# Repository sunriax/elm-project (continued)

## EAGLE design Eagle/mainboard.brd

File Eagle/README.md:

# elmProject EAGLE files
## Mainboard

### Files
1. Library:
		mainboard.lbr

1. Schematic:
		mainboard.sch
		schematic.pdf

1. Board:
		mainboard.brd
		layout.pdf

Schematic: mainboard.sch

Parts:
ANT1: SWRA092B
C1, C14, C15, C17, C94, C95, C96, C97, C99, C100, C122, C183, C186, C189, C193, C196, C199, C202, C206, C209, C212, C215, C228: 100n; C0402
C2, C5, C6, C7, C20, C21, C22, C29, C30, C34, C35, C36, C43, C51, C52, C53, C62, C63, C64, C73, C74, C75, C85, C86: 47n; C0402
C3, C4, C8, C9, C10, C23, C24, C25, C31, C37, C38, C39, C44, C54, C55, C56, C65, C66, C69, C76, C77, C78, C247: 470n; C0402
C11, C12, C26, C27, C32, C40, C41, C49, C57, C58, C70, C71, C79, C80: 4,7u; C0603
C13, C42, C59, C72, C81, C225, C226: 100u; C1206
C16: 4.7u; C0603
C18, C28, C33, C50, C250: 47u; C0603
C19, C48, C236, C237, C238, C248, C249: 470n; C0603
C45, C82, C83, C84, C87, C89, C90, C123, C124, C125, C182, C185, C188, C192, C195, C198, C201, C205, C208, C211, C214, C233, C234, C235, C243, C244, C245, C246: 10n; C0402
C46, C47: 47n; C0603
C60, C61, C177, C227, C251, C266, C267, C268, C269, C270: 10n; C0603
C67, C111, C118, C158, C159, C160: 4,7µF; C0603
C68, C142, C143, C161: 10µF; C0603
C88, C91, C203, C216, C229: 10u; C0603
C92, C93: 12p; C0402
C98: 10p; C0402
C101, C180, C190: 1u; C0603
C102: 1u; C0402
C103: 2u2; C0603
C104, C119, C178, C179: 18p; C0402
C105, C106, C112, C113: 220pF; C0603
C107, C108, C109, C110, C114, C115, C116, C117: 22pF; C0603
C120, C121: 1p; C0402
C126, C127: 0,1µF; C0603
C128, C131, C132, C133, C135, C136, C137, C138, C139: 1µF; C0603
C129, C130: 33pF; C0402
C134: 2,2µF; C0603
C145, C146: 22µF; C0603
C148, C149: 47µF; C0603
C151, C152: 68µF; C1206
C154, C156: 4,7µ; C0603
C157: 2,2µF; C1206K
C181, C184, C187, C191, C194, C197, C200, C204, C207, C210, C213: 1n; C0402
C217, C218, C219, C220, C221, C222, C223, C224, C230, C231, C232, C239, C240, C241, C242: 47p; C0402
C252: 22p; C0402
D1, D4, D5, D6, D7, D10, D11, D12, D38, D39, D40, D41: WE-TVS_824015; WE-TVS_SOT23-6L
D2, D8, D35, D36, D42: WE-TVS_824011; WE-TVS_SOT23-5L
D3, D37: BAT6202VH6327XTSA1-ND; SOD523
D9: CZSH5-40-TR-ND; SOT223
FRAME1, FRAME2, FRAME3, FRAME4, FRAME5, FRAME6, FRAME7, FRAME8, FRAME9, FRAME10: HTL-A3-HA3H; HTL-A3-H
G1: 10MM_SM_COIN_CELL_CLIP
IC1: S25FL128P
IC5: FT240X; SSOP24-0.635-8.65X4MM
IC6: CC2540; QFN40-6X6
IC7: Arietta/FPGA; LT8602
IC8: Boards; LT8602
IC9: TUSB4041I; HTQFP-64-EXP
IC10: LTC2947
IC11: 74AHC1G32DCK; SC70-5
IC12, IC13: 74AHC1G04DCK; SC70-5
IC14: EEPROM; SOIC-8
IC16: MT48LC16M16A2; TSOP54-400
K1: 61001221121
K2: 61000418221
K3: 691321100002
K4, K5: 61300511821
L1, L2: 1u; L2012C
L3: 6n8; L2012C
L4, L7, L10: 220 Ohm @ 100 Mhz; WE-KI_0603_B
L5, L6: 4,3n; WE-KI_0402A
L8: 12n; WE-KI_0402A
L13, L17: 10µH; NR6028T100M
L14, L18: 4,7µH; NR6028T100M
L15, L21: 2,2µH; IHHP-0806AZ-01
L16, L24: 1,1µH; SRN3012TA
LED_BANK1_FAULT, LED_BANK1_ONLINE, LED_BANK2_FAULT, LED_BANK2_ONLINE: 0.7; SMARTLED-TTW
LED_BLUETOOTH: 0.7; SMARTLED-TTW
LED_DONE: 0.7; SMARTLED-TTW
PAD1, PAD2, PAD3, PAD4, PAD5, PAD6, PAD7, PAD8, PAD9, PAD10, PAD11, PAD12, PAD13, PAD14, PAD15, PAD16: SMD2; SMD1,27-2,54
Q1: SPD30P06PTO252; TO252
Q2: 24MHz; CTS406
Q3: 32MHz; CTS402_3.2X2.5
R1, R20, R25: 33; R0402
R2, R21, R61: 0; R0402
R3, R9, R10, R15: 4k7; R0402
R4, R5, R6, R14, R56, R58: 1k; R0402
R7: 200; R0402
R8, R11, R12, R13, R16, R18, R19, R34, R35, R40, R41, R42: 100; R0402
R17, R22, R23, R24: 330; R0402
R26, R27, R28, R29, R30, R31, R32, R33: 10Ohm; R0603
R36, R62: 1; R0402
R37, R38, R95, R107: 10k; R0603
R39: 56k; R0603
R43: 1M; R0805
R44: 9k53 1%; R0603
R45: 90k9 1%; R0603
R46: 10k 1%; R0603
R47, R48, R49, R50, R51, R52, R53, R54: 27; R0402
R55: 25; R0402
R57: 1k; R0603
R63, R64: 1k5; R0402
R65: 10k; R0402
R84, R96, R103: 68k; R0603
R85, R97: 400k; R0603
R86, R98: 100k; R0603
R87, R99: 715k; R0603
R88, R90, R92, R94, R100, R102, R104, R106: 180k; R0603
R89, R101: 412k; R0603
R91: 47k; R0603
R93, R105: 226k; R0603
R120, R121: 22Ohm; R0603
R122: 100k; R1206
R123: 2Ohm; R1206
R124, R125: 4,02k; R1206
R126: 10m; R1206
RN1, RN2, RN3, RN4, RN5, RN6, RN7, RN8, RN9, RN10, RN11, RN12, RN16, RN17, RN18, RN19, RN20, RN23, RN24, RN25, RN26, RN27, RN28, RN29, RN30, RN31, RN32, RN33, RN34: 100; EXBV8V
RN15: 10k; EXBV8V
RN21, RN22, RN36, RN37, RN38, RN39, RN40, RN41, RN42, RN43: 33; EXBV8V
RN35: 1k; EXBV8V
RN44: 25; EXBV8V
S1, S2, S3: TASTER_SMD
TP3, TP4: PTR1TP06SQ; TP06SQ
U1: XC7A100TFTG256; FT256
U$1: ARIETTA
U$4, U$11: NTD4969NT4G_N-MOS; TO252
U$5, U$6: ASE
U$7, U$8: NUF2221W1
U$9, U$10: MF-SMDF200; MF-SMDF050
X1, X2, X3, X4: FAB64S
X5: ABLS2-4.000MHZ-D4Y-T
X6, X7: USB-A003
X8: JMP2

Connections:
$N299: C225.1, C226.1, C227.2, D36.3 (1), D36.4 (2), D36.5 (VDD), U$10.2, X6.4, X7.4
+1V1_EXT: C116.1, C152.1, L7.1, L24.P$2 (OUT), PAD16.1, R33.2
+1V1_HUB: C194.1, C195.1, C196.1, C197.1, C198.1, C199.1, C200.1, C201.1, C202.1, C203.1, C204.1, C205.1, C206.1, C207.1, C208.1, C209.1, C210.1, C211.1, C212.1, C213.1, C214.1, C215.1, C216.1, IC9.19 (VDD), IC9.25 (VDD), IC9.37 (VDD), IC9.45 (VDD), IC9.53 (VDD), IC9.60 (VDD), IC9.63 (VDD), L7.2
+1V8_EXT: C117.1, C149.1, D6.1, D38.1, D39.1, D40.3 (2), L21.P$2 (OUT), PAD14.1, R32.2, X1.B32, X2.B32, X3.B32, X4.B32
+1V8_INT: C20.1, C21.1, C22.1, C23.1, C24.1, C25.1, C26.1, C27.1, C28.1, C110.1, C148.1, L1.2, L15.P$2 (OUT), PAD6.1, R28.2, U1.F8 (VCCBATT_0), U1.G10 (VCCAUX), U1.J10 (VCCAUX), U1.K11 (VCCAUX), U1.L10 (VCCAUX)
+1V_INT: C29.1, C30.1, C31.1, C32.1, C33.1, C34.1, C35.1, C36.1, C37.1, C38.1, C39.1, C40.1, C41.1, C42.1, C43.1, C109.1, C151.1, L16.P$2 (OUT), PAD8.1, R29.2, U1.E10 (VCCBRAM), U1.F7 (VCCINT), U1.F9 (VCCINT), U1.F11 (VCCBRAM), U1.G6 (VCCINT), U1.H9 (VCCINT), U1.J6 (VCCINT), U1.K9 (VCCINT), U1.L8 (VCCINT)
+3V3_ARIETTA: C82.2, C83.2, C89.2, C90.2, D3.C, D4.5 (VDD), D5.5 (VDD), D7.5 (VDD), D8.5 (VDD), R37.1, RN15.5 (2), RN15.6 (2), RN15.7 (2), RN15.8 (2), U$1.5 (3V3)
+3V3_BLUETOOTH: C94.2, C95.2, C96.2, C97.2, C98.2, C99.2, C100.2, C101.2, C103.1, C123.2, C124.2, C125.2, C252.2, D10.5 (VDD), D11.5 (VDD), D12.5 (VDD), IC6.4 (DVDD_USB), IC6.10 (DVDD2), IC6.21 (AVDD5), IC6.24 (AVDD3), IC6.27 (AVDD2), IC6.28 (AVDD1), IC6.29 (AVDD4), IC6.31 (AVDD6), IC6.39 (DVDD1), L4.2
+3V3_EXT: C60.1, C61.1, C62.1, C63.1, C64.1, C65.1, C66.1, C69.1, C70.1, C71.1, C72.1, C73.1, C74.1, C75.1, C76.1, C77.1, C78.1, C79.1, C80.1, C81.1, C115.1, C118.1, C146.1, C159.1, C177.2, C251.1, D1.5 (VDD), D2.5 (VDD), D6.6 (4), D35.5 (VDD), D38.6 (4), D39.6 (4), D40.6 (4), D42.4 (2), D42.5 (VDD), IC8.BIAS, IC8.PVIN3, IC8.PVIN4, IC11.5 (VCC), IC12.5 (VCC), IC13.5 (VCC), L10.1, L18.2 (OUT), PAD11.1, R2.2, R31.2, R107.1, U1.A6 (VCCO_35), U1.A16 (VCCO_15), U1.B3 (VCCO_35), U1.B13 (VCCO_15), U1.C10 (VCCO_15), U1.D7 (VCCO_35), U1.E4 (VCCO_35), U1.E14 (VCCO_15), U1.F1 (VCCO_35), U1.H15 (VCCO_15), U1.J2 (VCCO_35), U1.J12 (VCCO_15), X1.B30, X2.B30, X3.B30, X4.B30, X8.1
+3V3_HUB: C181.1, C182.1, C183.1, C184.1, C185.1, C186.1, C187.1, C188.1, C189.1, C190.1, C191.1, C192.1, C193.1, C228.1, IC9.2 (VDD33), IC9.20 (VDD33), IC9.31 (VDD33), IC9.48 (VDD33), IC14.8 (VCC), L10.2, R56.1, R57.2, R63.1, R64.2, U$7.5 (VBUS), U$8.5 (VBUS)
+3V3_INT: C1.1, C2.2, C3.2, C4.2, C5.1, C6.1, C7.1, C8.1, C9.1, C10.1, C11.1, C12.1, C13.1, C14.1, C15.1, C16.1, C18.1, C19.1, C51.1, C52.1, C53.1, C54.1, C55.1, C56.1, C57.1, C58.1, C59.1, C84.1, C85.1, C86.1, C87.1, C108.1, C111.1, C122.1, C131.1, C145.1, C158.1, C230.1, C231.1, C232.1, C233.1, C234.1, C235.1, C236.1, C237.1, C238.1, C239.1, C240.1, C241.1, C242.1, C243.1, C244.1, C245.1, C246.1, C247.1, C248.1, C249.1, C250.1, C270.2, D37.C, D41.5 (VDD), IC1.VCC, IC5.18 (VCC), IC7.BIAS, IC7.PVIN3, IC7.PVIN4, IC10.AD0, IC10.OVDD, IC16.1 (VDD), IC16.3 (VDDQ), IC16.9 (VDDQ), IC16.14 (VDD), IC16.27 (VDD), IC16.43 (VDDQ), IC16.49 (VDDQ), K2.3, L14.2 (OUT), PAD4.1, R3.2, R5.2, R6.2, R7.1, R9.1, R10.1, R14.1, R15.1, R27.2, R38.1, R65.2, R95.1, U1.L6 (VCCO_0), U1.L16 (VCCO_14), U1.M3 (VCCO_34), U1.M13 (VCCO_14), U1.N10 (VCCO_14), U1.P7 (VCCO_14), U1.R4 (VCCO_34), U1.R14 (VCCO_14), U1.T1 (VCCO_34), U1.T11 (VCCO_14), U$5.1 (TRI), U$5.4 (VDD), U$6.1 (TRI), U$6.4 (VDD)
+5V_EXT: C114.1, C143.1, C229.1, C266.2, C267.2, C268.2, C269.2, D6.3 (2), D6.5 (VDD), D38.3 (2), D38.5 (VDD), D39.3 (2), D39.5 (VDD), D40.1, D40.5 (VDD), L17.2 (OUT), PAD10.1, R30.2, R45.1, U$10.1, X1.B31, X2.B31, X3.B31, X4.B31
+5V_INT: C46.1, C47.1, C48.1, C49.1, C50.1, C107.1, C142.1, L13.2 (OUT), PAD1.1, R26.2, U$1.1 (5V)
ACDRVPIN: K4.2, Q1.1 (G), R122.2, R124.1
ACN: C132.1, C133.1, IC10.AVCC, IC10.DVCC, IC10.IP_1 (IP), IC10.IP_2 (IP), IC10.IP_3 (IP), IC10.IP_4 (IP), IC10.IP_5 (IP), IC10.IP_6 (IP), K5.1, K5.2, K5.3, Q1.3 (D), R126.2
ACPPIN: K5.4, R126.1, U$11.3 (D)
ARIETTA_IO0: D4.1, RN1.8 (2), X1.B7, X2.B7
ARIETTA_IO1: D4.3 (2), RN1.7 (2), X1.A6, X2.A7
ARIETTA_IO2: D4.4 (3), RN1.6 (2), X1.B6, X2.B6
ARIETTA_IO3: D4.6 (4), RN1.5 (2), X1.B5, X2.A6
ARIETTA_IO4: D5.3 (2), RN2.5 (2), X1.A5, X2.B5
ARIETTA_IO5: D5.1, RN2.6 (2), X1.B4, X2.A5
AVCCPIN: D9.4 (C), K4.3, Q1.2 (S), R123.2, U$4.3 (D)
BANK1_AD*N0: RN3.5 (2), X3.B22
BANK1_AD*N1: RN3.8 (2), X3.B24
BANK1_AD*N2: RN4.8 (2), X3.A26
BANK1_AD*N3: RN5.7 (2), X3.A21
BANK1_AD*N4: RN6.7 (2), X3.A28
BANK1_AD*N5: RN6.5 (2), X3.B27
BANK1_AD*N6: RN7.8 (2), X3.A24
BANK1_AD*N7: RN7.5 (2), X3.B26
BANK1_AD*P0: RN3.6 (2), X3.A22
BANK1_AD*P1: RN3.7 (2), X3.B23
BANK1_AD*P2: RN4.7 (2), X3.A25
BANK1_AD*P3: RN5.8 (2), X3.B21
BANK1_AD*P4: RN6.8 (2), X3.B28
BANK1_AD*P5: RN6.6 (2), X3.A27
BANK1_AD*P6: RN7.7 (2), X3.A23
BANK1_AD*P7: RN7.6 (2), X3.B25
BANK1_FAULT: IC12.2 (I), R41.2, U1.E6 (IO_0_35)
BANK1_MRCC/SRCC0: RN8.6 (2), X1.A25, X4.B25
BANK1_MRCC/SRCC1: RN8.5 (2), X1.B25, X4.B24
BANK1_MRCC/SRCC2: RN8.7 (2), X1.B26, X4.B26
BANK1_MRCC/SRCC3: RN8.8 (2), X1.A26, X4.B27
BANK1_MRCC/SRCC4: RN9.7 (2), X1.B22, X4.A21
BANK1_MRCC/SRCC5: RN9.8 (2), X1.B21, X4.A20
BANK1_MRCC/SRCC6: RN9.6 (2), X1.A22, X2.B22
BANK1_MRCC/SRCC7: RN9.5 (2), X1.A23, X2.B23
BANK1_T0_0: RN4.5 (2), X1.B24, X4.B23
BANK1_T0_1: RN4.6 (2), X1.A24, X4.A23
BANK1_T0_2: RN5.6 (2), X1.B20, X4.B20
BANK1_T0_3: RN5.5 (2), X1.B23
BANK1_T2_0: RN10.8 (2), X1.A21, X2.B21, X4.A17
BANK1_T2_1: RN10.7 (2), X1.A20, X2.B20, X4.B17
BANK1_T2_2: RN10.6 (2), X1.B19, X2.B19, X4.A14
BANK1_T2_3: RN11.7 (2), X1.A18
BANK1_T2_4: RN10.5 (2), X1.A19, X2.B18, X4.B14
BANK1_T2_5: RN11.8 (2), X1.B18
BANK1_T2_6: RN11.6 (2), X1.B17
BANK1_T2_7: RN11.5 (2), X1.A17, X2.B17
BANK1_T3_0: RN12.8 (2), X1.A28, X2.B28
BANK1_T3_1: RN12.7 (2), X1.B28, X2.B27
BANK1_T3_2: RN12.6 (2), X1.A27, X2.B26
BANK1_T3_3: RN12.5 (2), X1.B27, X2.B25
BANK2_A0: RN30.6 (2), X1.A15, X3.A12, X4.A10
BANK2_A1: RN30.5 (2), X1.B14, X3.B11, X4.B9
BANK2_A2: RN31.8 (2), X1.B12, X3.B9, X4.B7
BANK2_A3: RN31.6 (2), X1.B13, X3.B10, X4.B8
BANK2_A4: RN31.7 (2), X1.A12, X3.A9, X4.A7
BANK2_A5: RN31.5 (2), X1.A13, X3.A10, X4.A8
BANK2_A6: RN32.7 (2), X1.B11, X3.B8, X4.B6
BANK2_A7: RN32.8 (2), X1.A11, X3.A8, X4.A6
BANK2_A8: RN32.5 (2), X1.B9, X3.B7, X4.B5
BANK2_A9: RN32.6 (2), X1.B10, X3.A7, X4.A5
BANK2_A10: RN33.8 (2), X1.A14, X3.A11, X4.A9
BANK2_A11: RN33.7 (2), X1.B15, X3.B12, X4.B10
BANK2_A12: RN33.5 (2), X1.B16, X4.A16
BANK2_A13: RN33.6 (2), X1.A16, X4.A15
BANK2_AD*N0: RN23.6 (2), X3.B19
BANK2_AD*N1: RN23.5 (2), X3.A19
BANK2_AD*N2: RN24.7 (2), X3.B13
BANK2_AD*N3: RN25.8 (2), X3.A15
BANK2_AD*N4: RN26.7 (2), X3.A16
BANK2_AD*N5: RN26.8 (2), X3.B16
BANK2_AD*N6: RN27.6 (2), X3.B17
BANK2_AD*N7: RN27.5 (2), X3.A17
BANK2_AD*P0: RN23.8 (2), X3.B20
BANK2_AD*P1: RN23.7 (2), X3.A20
BANK2_AD*P2: RN24.8 (2), X3.A13
BANK2_AD*P3: RN25.7 (2), X3.B15
BANK2_AD*P4: RN26.5 (2), X3.B14
BANK2_AD*P5: RN26.6 (2), X3.A14
BANK2_AD*P6: RN27.8 (2), X3.B18
BANK2_AD*P7: RN27.7 (2), X3.A18
BANK2_FAULT: IC13.2 (I), R42.2, U1.D10 (IO_0_15)
BANK2_MRCC/SRCC0: RN28.8 (2), X2.A10, X3.A5
BANK2_MRCC/SRCC1: RN28.7 (2), X2.B10, X3.B5
BANK2_MRCC/SRCC2: RN28.6 (2), X2.A8, X3.B2
BANK2_MRCC/SRCC3: RN28.5 (2), X2.B8, X3.B1
BANK2_MRCC/SRCC4: RN29.7 (2), X2.A9, X3.B4
BANK2_MRCC/SRCC5: RN29.8 (2), X2.B9, X3.B3
BANK2_MRCC/SRCC6: RN29.6 (2), X2.B11, X3.B6
BANK2_MRCC/SRCC7: RN29.5 (2), X2.A11, X3.A6
BANK2_T0_0: RN24.6 (2), X2.A12, X4.A11
BANK2_T0_1: RN24.5 (2), X2.B12, X4.B11
BANK2_T0_2: RN25.5 (2), X2.A14, X4.A13
BANK2_T0_3: RN25.6 (2), X2.A13, X4.B13
BANK2_T2_0: RN30.7 (2), X2.A15, X4.B15
BANK2_T2_1: RN30.8 (2), X2.A16, X4.B16
BANK2_T3_0: RN34.7 (2), X1.A8, X2.B14
BANK2_T3_1: RN34.8 (2), X1.A7, X2.B13
BANK2_T3_2: RN34.6 (2), X1.A9, X2.B15
BANK2_T3_3: RN34.5 (2), X1.A10, X2.B16
BANK_FAULT: D35.4 (2), R62.2, X1.B29, X2.B29, X3.B29, X4.B29
BLUETOOTH_EXT0: D11.1, RN18.8 (2), X2.A17, X4.A18
BLUETOOTH_EXT1: D11.3 (2), RN18.7 (2), X2.A18, X4.B18
BLUETOOTH_EXT2: D10.6 (4), RN18.6 (2), X2.A22, X4.B22
BLUETOOTH_EXT3: D10.4 (3), RN18.5 (2), X2.A21, X4.B21
BLUETOOTH_EXT4: D10.1, RN19.8 (2), X2.A20, X4.A19
BLUETOOTH_EXT5: D10.3 (2), RN19.7 (2), X2.A19, X4.B19
BLUETOOTH_EXT6: D11.6 (4), RN19.6 (2), X2.A23, X4.A22
BLUETOOTH_EXT7: D11.4 (3), RN19.5 (2), X2.A24, X4.A24
BLUETOOTH_EXT8: D12.1, RN20.8 (2), X2.A25, X4.A25
BLUETOOTH_EXT9: D12.3 (2), RN20.7 (2), X2.A26, X4.A26
BLUETOOTH_EXT10: D12.6 (4), RN20.6 (2), X2.A27, X4.A27
BLUETOOTH_EXT11: D12.4 (3), RN20.5 (2), X2.A28, X4.A28
BLUETOOTH_INT0: RN21.8 (2), U1.J1 (IO_L22N_T3_35)
BLUETOOTH_INT1: RN21.7 (2), U1.K1 (IO_L22P_T3_35)
BLUETOOTH_INT2: RN21.6 (2), U1.H3 (IO_L21N_T3_DQS_35)
BLUETOOTH_INT3: RN21.5 (2), U1.J3 (IO_L21P_T3_DQS_35)
BLUETOOTH_INT4: RN22.8 (2), U1.L2 (IO_L23N_T3_35)
BLUETOOTH_INT5: RN22.7 (2), U1.L3 (IO_L23P_T3_35)
BLUETOOTH_INT6: RN22.6 (2), U1.K2 (IO_L24N_T3_35)
BLUETOOTH_INT7: RN22.5 (2), U1.K3 (IO_L24P_T3_35)
BLUETOOTH_USB_DM: C222.1, IC6.3 (USB_N), R51.1
BLUETOOTH_USB_DP: C223.1, IC6.2 (USB_P), R53.1, R63.2
CMSRCPIN: K4.1, R125.1
CONFIG_CCLK: IC1.SCK, R24.1, U1.E8 (CCLK_0)
CONFIG_D00_MOSI: R12.1, U1.J13 (IO_L1P_T0_D00_MOSI_14)
CONFIG_D01_DIN: R11.2, R18.2, U1.J14 (IO_L1N_T0_D01_DIN_14)
CONFIG_D02_DQ2: R13.1, U1.K15 (IO_L2P_T0_D02_14)
CONFIG_D03_DQ3: R16.2, U1.K16 (IO_L2N_T0_D03_14)
CONFIG_DOUT: R19.2, U1.T12 (IO_L15N_T2_DQS_DOUT_CSO_B_14)
CONFIG_FCS_B: IC1.CS#, R15.2, U1.L12 (IO_L6P_T0_FCS_B_14)
DONE: R7.2, R8.1, R22.1, U1.H10 (DONE_0)
FIFO0: IC5.24 (DATA0), U1.P15 (IO_L8P_T1_D11_14)
FIFO1: IC5.4 (DATA1), U1.M14 (IO_L4N_T0_D05_14)
FIFO2: IC5.2 (DATA2), U1.N16 (IO_L7N_T1_D10_14)
FIFO3: IC5.9 (DATA3), U1.L14 (IO_L4P_T0_D04_14)
FIFO4: IC5.1 (DATA4), U1.P16 (IO_L8N_T1_D12_14)
FIFO5: IC5.7 (DATA5), U1.K13 (IO_L5P_T0_D06_14)
FIFO6: IC5.8 (DATA6), U1.L13 (IO_L5N_T0_D07_14)
FIFO7: IC5.5 (DATA7), U1.M16 (IO_L7P_T1_D09_14)
FIFO_USB_DM: C221.1, IC5.14 (USBDM), R52.1
FIFO_USB_DP: C224.1, IC5.13 (USBDP), R54.1, R64.1
FPGA_CCLK1: U1.N14 (IO_L12P_T1_MRCC_14), U$5.3 (OUT)
FPGA_CCLK2: U1.P14 (IO_L12N_T1_MRCC_14), U$6.3 (OUT)
GND: C1.2, C2.1, C3.1, C4.1, C5.2, C6.2, C7.2, C8.2, C9.2, C10.2, C11.2, C12.2, C13.2, C14.2, C15.2, C16.2, C17.2, C18.2, C19.2, C20.2, C21.2, C22.2, C23.2, C24.2, C25.2, C26.2, C27.2, C28.2, C29.2, C30.2, C31.2, C32.2, C33.2, C34.2, C35.2, C36.2, C37.2, C38.2, C39.2, C40.2, C41.2, C42.2, C43.2, C44.2, C46.2, C47.2, C48.2, C49.2, C50.2, C51.2, C52.2, C53.2, C54.2, C55.2, C56.2, C57.2, C58.2, C59.2, C60.2, C61.2, C62.2, C63.2, C64.2, C65.2, C66.2, C67.2, C68.2, C69.2, C70.2, C71.2, C72.2, C73.2, C74.2, C75.2, C76.2, C77.2, C78.2, C79.2, C80.2, C81.2, C82.1, C83.1, C84.2, C85.2, C86.2, C87.2, C88.1, C89.1, C90.1, C91.1, C92.1, C93.1, C94.1, C95.1, C96.1, C97.1, C98.1, C99.1, C100.1, C101.1, C102.2, C103.2, C105.2, C106.2, C111.2, C112.2, C113.2, C118.2, C121.2, C122.2, C123.1, C124.1, C125.1, C126.1, C127.1, C129.2, C130.2, C131.2, C132.2, C133.2, C135.2, C142.2, C143.2, C145.2, C146.2, C148.2, C149.2, C151.2, C152.2, C154.2, C156.2, C157.2, C158.2, C159.2, C160.2, C161.2, C177.1, C178.1, C179.1, C180.1, C181.2, C182.2, C183.2, C184.2, C185.2, C186.2, C187.2, C188.2, C189.2, C190.2, C191.2, C192.2, C193.2, C194.2, C195.2, C196.2, C197.2, C198.2, C199.2, C200.2, C201.2, C202.2, C203.2, C204.2, C205.2, C206.2, C207.2, C208.2, C209.2, C210.2, C211.2, C212.2, C213.2, C214.2, C215.2, C216.2, C217.1, C218.2, C219.1, C220.2, C221.2, C222.2, C223.2, C224.2, C225.2, C226.2, C227.1, C228.2, C229.2, C230.2, C231.2, C232.2, C233.2, C234.2, C235.2, C236.2, C237.2, C238.2, C239.2, C240.2, C241.2, C242.2, C243.2, C244.2, C245.2, C246.2, C247.2, C248.2, C249.2, C250.2, C251.2, C252.1, C266.1, C267.1, C268.1, C269.1, C270.1, D1.2 (GND), D2.2 (GND), D4.2 (GND), D5.2 (GND), D6.2 (GND), D7.2 (GND), D8.2 (GND), D10.2 (GND), D11.2 (GND), D12.2 (GND), D35.2 (GND), D36.2 (GND), D38.2 (GND), D39.2 (GND), D40.2 (GND), D41.2 (GND), D42.2 (GND), G1.-, IC1.GND, IC5.6 (GND), IC5.19 (GND1), IC6.1 (DGND_USB), IC6.EXP@1 (EXP16), IC6.EXP@2 (EXP16), IC6.EXP@3 (EXP16), IC6.EXP@4 (EXP16), IC6.EXP@5 (EXP16), IC6.EXP@6 (EXP16), IC6.EXP@7 (EXP16), IC6.EXP@8 (EXP16), IC6.EXP@9 (EXP16), IC6.EXP@10 (EXP16), IC6.EXP@11 (EXP16), IC6.EXP@12 (EXP16), IC6.EXP@13 (EXP16), IC6.EXP@14 (EXP16), IC6.EXP@15 (EXP16), IC6.EXP@16 (EXP16), IC7.GND_1 (GND), IC7.GND_2 (GND), IC7.GND_3 (GND), IC7.GND_4 (GND), IC7.GND_5 (GND), IC7.GND_6 (GND), IC7.GND_7 (GND), IC7.GND_8 (GND), IC7.POREN, IC7.SYNC, IC8.GND_1 (GND), IC8.GND_2 (GND), IC8.GND_3 (GND), IC8.GND_4 (GND), IC8.GND_5 (GND), IC8.GND_6 (GND), IC8.GND_7 (GND), IC8.GND_8 (GND), IC8.POREN, IC8.SYNC, IC9.EXP (GND), IC10.AGND, IC10.ALERT, IC10.DGND, IC10.DGND_2 (DGND), IC10.GPIO, IC11.3 (GND), IC12.3 (GND), IC13.3 (GND), IC14.4 (GND), IC16.6 (VSSQ), IC16.12 (VSSQ), IC16.28 (VSS), IC16.41 (VSS), IC16.46 (VSSQ), IC16.52 (VSSQ), IC16.54 (VSS), K1.1, K1.12, K2.1, K3.1, K4.4, K4.5, L2.2, L6.1, LED_BANK1_FAULT.C@1 (C), LED_BANK1_ONLINE.C@1 (C), LED_BANK2_FAULT.C@1 (C), LED_BANK2_ONLINE.C@1 (C), LED_BLUETOOTH.C@1 (C), LED_DONE.C@1 (C), R4.2, R39.2, R44.1, R46.1, R84.1, R86.1, R88.1, R90.1, R92.1, R94.1, R96.1, R98.1, R100.1, R102.1, R104.1, R106.1, R121.2, R122.1, RN35.5 (2), RN35.6 (2), RN35.7 (2), RN35.8 (2), S1.1 (S), S1.2 (S1), S2.3, S2.4 (P1), S3.3, S3.4 (P1), U1.A1 (GND), U1.A11 (GND), U1.B8 (GND), U1.C5 (GND), U1.C15 (GND), U1.D2 (GND), U1.D12 (GND), U1.E9 (GND), U1.F6 (GND), U1.F10 (GND), U1.F16 (GND), U1.G3 (GND), U1.G9 (GND), U1.G13 (GND), U1.H6 (GND), U1.J9 (GND), U1.J11 (GND), U1.K4 (GND), U1.K6 (GND), U1.K7 (DXN_0), U1.K8 (DXP_0), U1.K14 (GND), U1.L1 (GND), U1.L11 (GND), U1.M8 (GND), U1.N5 (GND), U1.N15 (GND), U1.P2 (GND), U1.P12 (GND), U1.R9 (GND), U1.T6 (GND), U1.T16 (GND), U$1.9 (GND), U$1.D6 (DEBUG_GND), U$5.2 (GND), U$6.2 (GND), U$7.2 (GND), U$8.2 (GND), X1.A29, X1.A30, X1.A31, X1.A32, X2.A29, X2.A30, X2.A31, X2.A32, X3.A29, X3.A30, X3.A31, X3.A32, X4.A29, X4.A30, X4.A31, X4.A32, X6.1, X7.1
I2C_SCL0: RN2.1, RN15.4 (1), U1.M12 (IO_L6N_T0_D08_VREF_14), U$1.12 (I2C_SCL0/SPI_CS2)
I2C_SCL1: RN15.3 (1), RN17.6 (2), U1.N12 (IO_L13N_T2_MRCC_14), U$1.37 (I2C_SCL1)
I2C_SDA0: RN2.2 (1), RN15.1, U1.N13 (IO_L11P_T1_SRCC_14), U$1.14 (I2C_SDA0/SPI_CS3)
I2C_SDA1: RN15.2 (1), RN17.5 (2), U1.T14 (IO_L10P_T1_D14_14), U$1.39 (I2C_SDA1)
INIT_B: R10.2, R23.1, U1.K10 (INIT_B_0)
JTAG_RXD: D2.3 (1), K1.11, R25.1
JTAG_TXD: D2.4 (2), K1.9, U$1.D4 (DEBUG_RXD)
unnamed: D1.6 (4), K1.2, U1.L7 (TCK_0)
unnamed: R1.1, U1.N8 (TDO_0)
unnamed: D1.4 (3), K1.4, R1.2
unnamed: D1.3 (2), K1.5, U1.N7 (TDI_0)
unnamed: D1.1, K1.6, U1.M7 (TMS_0)
unnamed: K1.3, R2.1
unnamed: R3.1, U1.E7 (CFGBVS_0)
unnamed: IC1.SO/PO7 (SO/DQ1), R11.1
unnamed: R17.2, U$1.29 (PC28)
unnamed: D41.6 (4), K2.4, R4.1, U1.M10 (M1_0)
unnamed: D41.4 (3), K2.2, R5.1, U1.M11 (M2_0)
unnamed: LED_DONE.A@1 (A), R8.2
unnamed: C44.1, C45.1, L1.1, U1.G8 (VCCADC_0)
unnamed: R25.2, U$1.D3 (DEBUG_TXD)
unnamed: R14.2, U1.L15 (IO_L3P_T0_DQS_PUDC_B_14)
unnamed: K3.2, U$9.1
unnamed: IC1.SI (SI/DQ0), R12.2
unnamed: IC1.HOLD# (HLD#/DQ3), R16.1
unnamed: IC1.WP#ACC (WP#/DQ2), R13.2
unnamed: C178.2, IC9.30 (XI), Q2.1, R43.1
unnamed: RN1.1, U$1.21 (PA29/I2S(RF))
unnamed: RN1.2 (1), U$1.19 (PA28/I2S(RK))
unnamed: RN1.3 (1), U$1.17 (PA27/I2S(RD))
unnamed: IC16.38 (CLK), R20.2
unnamed: RN1.4 (1), U$1.15 (PA26/I2S(TD))
unnamed: R58.1, R61.1, U$1.D2 (DEBUG_EN5V)
unnamed: C17.1, IC5.3 (VCCIO), IC5.15 (3V3OUT), IC5.16 (RESET#)
unnamed: IC5.23 (CBUS5), U1.M1 (IO_L2N_T0_34)
unnamed: IC16.15 (DQML), RN36.4 (1)
unnamed: C107.2, IC7.FB1, R87.1, R88.2
unnamed: PAD2.1, R26.1, R87.2
unnamed: R22.2, U$1.35 (PC2)
unnamed: R23.2, U$1.32 (PC31)
unnamed: R24.2, U$1.30 (PC27)
unnamed: R18.1, U$1.26 (PA7)
unnamed: R19.1, U$1.24 (PA1)
unnamed: IC11.4 (O), R62.1
unnamed: R35.2, U1.G11 (IO_25_15)
unnamed: PAD3.1, R27.1, R89.2
unnamed: PAD5.1, R28.1, R93.2
unnamed: PAD7.1, R29.1, R91.2
unnamed: IC7.SW4, L16.P$1 (IN)
unnamed: PAD9.1, R30.1, R99.2
unnamed: PAD12.1, R31.1, R101.2
unnamed: PAD13.1, R32.1, R105.2
unnamed: IC8.SW4, L24.P$1 (IN)
unnamed: PAD15.1, R33.1, R103.2
unnamed: R36.1, U$1.2 (VBAT)
unnamed: IC5.21 (RXF#), U1.M4 (IO_L1N_T0_34)
unnamed: IC5.20 (TXE#), U1.M2 (IO_L2P_T0_34)
unnamed: IC5.11 (RD#), U1.L5 (IO_0_34)
unnamed: IC5.12 (WR#), U1.L4 (IO_L1P_T0_34)
unnamed: RN2.4 (1), U$1.13 (PA25/I2S(TF))
unnamed: RN2.3 (1), U$1.11 (PA24/I2S(TK))
unnamed: R61.2, U$1.D1 (DEBUG_3V3)
unnamed: RN10.4 (1), U1.G2 (IO_L17P_T2_35)
unnamed: RN11.1, U1.G1 (IO_L17N_T2_35)
unnamed: IC11.2 (I1), IC13.4 (O)
unnamed: IC11.1 (I0), IC12.4 (O)
unnamed: C179.2, IC9.29 (XO), Q2.3 (2), R43.2
unnamed: IC9.22 (USB_DM_UP), U$1.4 (USBA_D-)
unnamed: C180.2, IC9.18 (GRSTZ)
unnamed: IC9.21 (USB_DP_UP), U$1.6 (USBA_D+)
unnamed: RN11.2 (1), U1.G4 (IO_L16N_T2_35)
unnamed: RN12.4 (1), U1.H1 (IO_L20N_T3_35)
unnamed: RN12.3 (1), U1.H2 (IO_L20P_T3_35)
unnamed: RN12.2 (1), U1.J4 (IO_L19N_T3_VREF_35)
unnamed: RN12.1, U1.J5 (IO_L19P_T3_35)
unnamed: RN11.4 (1), U1.H4 (IO_L18N_T2_35)
unnamed: RN11.3 (1), U1.H5 (IO_L18P_T2_35)
unnamed: R125.2, U$4.2 (S), U$11.2 (S)
unnamed: RN8.3 (1), U1.E3 (IO_L11P_T1_SRCC_35)
unnamed: RN8.1, U1.C4 (IO_L12N_T1_MRCC_35)
unnamed: RN8.4 (1), U1.D3 (IO_L11N_T1_SRCC_35)
unnamed: RN10.3 (1), U1.G5 (IO_L16P_T2_35)
unnamed: RN10.2 (1), U1.E1 (IO_L15N_T2_DQS_35)
unnamed: RN10.1, U1.F2 (IO_L15P_T2_DQS_35)
unnamed: RN9.4 (1), U1.F3 (IO_L14N_T2_SRCC_35)
unnamed: RN9.3 (1), U1.F4 (IO_L14P_T2_SRCC_35)
unnamed: RN9.1, U1.E5 (IO_L13N_T2_MRCC_35)
unnamed: RN9.2 (1), U1.F5 (IO_L13P_T2_MRCC_35)
unnamed: RN8.2 (1), U1.D4 (IO_L12P_T1_MRCC_35)
unnamed: RN7.1, U1.B1 (IO_L9N_T1_DQS_AD7N_35)
unnamed: RN7.2 (1), U1.C1 (IO_L9P_T1_DQS_AD7P_35)
unnamed: RN4.1, U1.A4 (IO_L3N_T0_DQS_AD5N_35)
unnamed: RN7.4 (1), U1.D1 (IO_L10N_T1_AD15N_35)
unnamed: RN7.3 (1), U1.E2 (IO_L10P_T1_AD15P_35)
unnamed: RN4.2 (1), U1.A5 (IO_L3P_T0_DQS_AD5P_35)
unnamed: RN4.3 (1), U1.A3 (IO_L4N_T0_35)
unnamed: RN6.4 (1), U1.A2 (IO_L8N_T1_AD14N_35)
unnamed: RN6.3 (1), U1.B2 (IO_L8P_T1_AD14P_35)
unnamed: RN6.2 (1), U1.C2 (IO_L7N_T1_AD6N_35)
unnamed: RN6.1, U1.C3 (IO_L7P_T1_AD6P_35)
unnamed: RN5.4 (1), U1.D5 (IO_L6N_T0_VREF_35)
unnamed: RN5.3 (1), U1.D6 (IO_L6P_T0_35)
unnamed: RN5.2 (1), U1.C6 (IO_L5N_T0_AD13N_35)
unnamed: RN5.1, U1.C7 (IO_L5P_T0_AD13P_35)
unnamed: RN4.4 (1), U1.B4 (IO_L4P_T0_35)
unnamed: RN3.3 (1), U1.B7 (IO_L1P_T0_AD4P_35)
unnamed: RN3.1, U1.B5 (IO_L2N_T0_AD12N_35)
unnamed: RN3.4 (1), U1.A7 (IO_L1N_T0_AD4N_35)
unnamed: RN3.2 (1), U1.B6 (IO_L2P_T0_AD12P_35)
unnamed: RN25.3 (1), U1.D9 (IO_L6N_T0_VREF_15)
unnamed: RN25.4 (1), U1.D8 (IO_L6P_T0_15)
unnamed: IC9.32 (USB_R1), R44.2
unnamed: R34.2, U1.K5 (IO_25_35)
unnamed: LED_BANK1_ONLINE.A@1 (A), R34.1
unnamed: C219.2, R48.1, U$7.3 (D2(I-))
unnamed: IC7.EN/UVLO, R85.1, R86.2
unnamed: C106.1, IC7.TRKSS2
unnamed: C105.1, IC7.TRKSS1
unnamed: IC7.RT, R84.2
unnamed: C156.1, IC7.INTVCC
unnamed: C108.2, IC7.FB2, R89.1, R90.2
unnamed: IC9.16 (USB_VBUS), R45.2, R46.2
unnamed: C109.2, IC7.FB4, R91.1, R92.2
unnamed: C110.2, IC7.FB3, R93.1, R94.2
unnamed: IC7.PG2, IC7.RUN3, IC7.RUN4, R95.2
unnamed: IC8.EN/UVLO, R97.1, R98.2
unnamed: C113.1, IC8.TRKSS2
unnamed: C112.1, IC8.TRKSS1
unnamed: IC8.RT, R96.2
unnamed: C154.1, IC8.INTVCC
unnamed: C115.2, IC8.FB2, R101.1, R102.2
unnamed: C114.2, IC8.FB1, R99.1, R100.2
unnamed: C116.2, IC8.FB4, R103.1, R104.2
unnamed: C117.2, IC8.FB3, R105.1, R106.2
unnamed: IC8.PG2, IC8.RUN3, IC8.RUN4, R107.2
unnamed: C220.1, R49.1, U$7.1 (D1(I+))
unnamed: C217.2, R47.1, U$8.3 (D2(I-))
unnamed: IC6.37 (P1_7), RN21.2 (1)
unnamed: C119.1, IC6.26 (RF_N), TP3.TP
unnamed: C104.1, IC6.25 (RF_P), TP4.TP
unnamed: C138.2, IC8.SW1, L17.1 (IN)
unnamed: C93.2, IC6.23 (XOSC_Q2), Q3.3 (2)
unnamed: C92.2, IC6.22 (XOSC_Q1), Q3.1
unnamed: U1.N3 (IO_L3P_T0_DQS_34), U$1.28 (UART_TXD)
unnamed: U1.N2 (IO_L3N_T0_DQS_34), U$1.27 (UART_RXD)
unnamed: IC7.SW3, L15.P$1 (IN)
unnamed: G1.+@1 (+), G1.+@2 (+), R36.2
unnamed: IC8.SW3, L21.P$1 (IN)
unnamed: IC6.30 (RBIAS), L3.2
unnamed: L3.1, R39.1
unnamed: C129.1, IC10.CKLI (CLKI), X5.1
unnamed: C130.1, IC10.CLKO, X5.2
unnamed: C126.2, C128.1, IC10.CFP
unnamed: C127.2, C128.2, IC10.CFM
unnamed: C135.1, IC10.BYP
unnamed: C134.1, IC10.VP, R120.1
unnamed: C134.2, IC10.VM, R121.1
unnamed: IC6.6 (P1_4), RN21.4 (1)
unnamed: C102.1, IC6.40 (DCOUPL)
unnamed: C136.1, IC7.BST1
unnamed: C137.1, IC7.BST2
unnamed: C138.1, IC8.BST1
unnamed: C139.1, IC8.BST2
unnamed: C104.2, C121.1, L5.2, L8.2
unnamed: C119.2, C120.1, L6.2, L8.1
unnamed: C157.1, R123.1
unnamed: R124.2, U$4.1 (G), U$11.1 (G)
unnamed: C218.1, R50.1, U$8.1 (D1(I+))
unnamed: C136.2, IC7.SW1, L13.1 (IN)
unnamed: C137.2, IC7.SW2, IC7.SW2_2 (SW2), L14.1 (IN)
unnamed: C139.2, IC8.SW2, IC8.SW2_2 (SW2), L18.1 (IN)
unnamed: D41.1, R6.1, U1.M9 (M0_0)
unnamed: ANT1.1, C120.2, L5.1
unnamed: IC16.7 (DQ3), RN40.1
unnamed: IC16.2 (DQ0), RN40.4 (1)
unnamed: IC6.11 (P1_0), RN20.1
unnamed: IC6.12 (P0_7), RN19.4 (1)
unnamed: IC6.13 (P0_6), RN19.3 (1)
unnamed: IC6.14 (P0_5), RN19.2 (1)
unnamed: IC6.15 (P0_4), RN19.1
unnamed: IC6.16 (P0_3), RN18.4 (1)
unnamed: IC6.17 (P0_2), RN18.3 (1)
unnamed: IC6.18 (P0_1), RN18.2 (1)
unnamed: IC6.19 (P0_0), RN18.1
unnamed: IC6.9 (P1_1), RN20.2 (1)
unnamed: IC6.8 (P1_2), RN20.3 (1)
unnamed: IC6.7 (P1_3), RN20.4 (1)
unnamed: IC16.39 (DQMH), RN36.3 (1)
unnamed: LED_BANK2_ONLINE.A@1 (A), R35.1
unnamed: IC6.5 (P1_5), RN21.3 (1)
unnamed: IC9.34 (USB_DM_DN1), R47.2
unnamed: IC6.36 (P2_0), RN22.1
unnamed: IC6.35 (P2_1), RN22.2 (1)
unnamed: IC6.34 (P2_2), RN22.3 (1)
unnamed: IC6.33 (P2_3/XOSC32K_Q2), RN22.4 (1)
unnamed: IC6.32 (P2_4/XOSC32K_Q1), R40.2
unnamed: RN23.3 (1), U1.C9 (IO_L1N_T0_AD0N_15)
unnamed: LED_BLUETOOTH.A@1 (A), R40.1
unnamed: LED_BANK2_FAULT.A@1 (A), R42.1
unnamed: IC9.42 (USB_DM_DN2), R48.2
unnamed: RN23.1, U1.C8 (IO_L1P_T0_AD0P_15)
unnamed: RN23.2 (1), U1.A8 (IO_L2P_T0_AD8P_15)
unnamed: RN32.2 (1), U1.H11 (IO_L19P_T3_A22_15)
unnamed: IC9.50 (USB_DM_DN3), R51.2
unnamed: RN23.4 (1), U1.A9 (IO_L2N_T0_AD8N_15)
unnamed: IC9.41 (USB_DP_DN2), R49.2
unnamed: IC9.33 (USB_DP_DN1), R50.2
unnamed: IC9.57 (USB_DM_DN4), R52.2
unnamed: IC9.49 (USB_DP_DN3), R53.2
unnamed: IC9.56 (USB_DP_DN4), R54.2
unnamed: IC14.1 (A0), RN35.1
unnamed: RN32.4 (1), U1.H12 (IO_L20P_T3_A20_15)
unnamed: IC14.2 (A1), RN35.2 (1)
unnamed: IC14.3 (A2), RN35.3 (1)
unnamed: IC14.7 (WP), RN35.4 (1)
unnamed: IC9.6 (SCL/SMBCLK), IC14.6 (SCL)
unnamed: IC9.5 (SDA/SMBDAT), IC14.5 (SDA)
unnamed: IC9.7 (SMBUSZ), R56.2
unnamed: IC9.13 (AUTOENZ/HS_SUSPEND), R57.1
unnamed: R58.2, U$1.D5 (DEBUG_WKUP)
unnamed: D9.1 (A), U$9.2
unnamed: RN32.1, U1.G12 (IO_L19N_T3_A21_VREF_15)
unnamed: IC16.16 (!WE), RN44.1
unnamed: IC16.17 (!CAS), RN44.2 (1)
unnamed: IC16.18 (!RAS), RN44.3 (1)
unnamed: RN36.5 (2), U1.R16 (IO_L9N_T1_DQS_D13_14)
unnamed: RN36.6 (2), U1.T15 (IO_L10N_T1_D15_14)
unnamed: RN36.8 (2), U1.R12 (IO_L15P_T2_DQS_RDWR_B_14)
unnamed: LED_BANK1_FAULT.A@1 (A), R41.1
unnamed: RN36.7 (2), U1.P13 (IO_L11N_T1_SRCC_14)
unnamed: IC16.20 (BA0), RN36.2 (1)
unnamed: IC16.21 (BA1), RN36.1
unnamed: IC16.23 (A0), RN37.1
unnamed: IC16.24 (A1), RN37.2 (1)
unnamed: IC16.25 (A2), RN37.3 (1)
unnamed: IC16.26 (A3), RN37.4 (1)
unnamed: IC16.22 (A10), RN39.1
unnamed: IC16.32 (A7), RN38.1
unnamed: IC16.31 (A6), RN38.2 (1)
unnamed: IC16.30 (A5), RN38.3 (1)
unnamed: IC16.29 (A4), RN38.4 (1)
unnamed: IC16.35 (A11), RN39.4 (1)
unnamed: RN24.1, U1.B9 (IO_L3P_T0_DQS_AD1P_15)
unnamed: RN24.2 (1), U1.A10 (IO_L3N_T0_DQS_AD1N_15)
unnamed: RN24.3 (1), U1.B10 (IO_L4P_T0_15)
unnamed: RN24.4 (1), U1.B11 (IO_L4N_T0_15)
unnamed: RN25.2 (1), U1.B12 (IO_L5P_T0_AD9P_15)
unnamed: RN25.1, U1.A12 (IO_L5N_T0_AD9N_15)
unnamed: RN32.3 (1), U1.H13 (IO_L20N_T3_A19_15)
unnamed: RN29.2 (1), U1.E12 (IO_L13P_T2_MRCC_15)
unnamed: RN26.4 (1), U1.A13 (IO_L7P_T1_AD2P_15)
unnamed: RN26.2 (1), U1.A14 (IO_L7N_T1_AD2N_15)
unnamed: RN26.3 (1), U1.C14 (IO_L8P_T1_AD10P_15)
unnamed: RN26.1, U1.B14 (IO_L8N_T1_AD10N_15)
unnamed: RN27.1, U1.B15 (IO_L9P_T1_DQS_AD3P_15)
unnamed: RN27.2 (1), U1.C16 (IO_L10P_T1_AD11P_15)
unnamed: RN27.3 (1), U1.A15 (IO_L9N_T1_DQS_AD3N_15)
unnamed: RN27.4 (1), U1.B16 (IO_L10N_T1_AD11N_15)
unnamed: RN28.1, U1.C11 (IO_L11P_T1_SRCC_15)
unnamed: RN28.2 (1), U1.C12 (IO_L11N_T1_SRCC_15)
unnamed: RN28.3 (1), U1.D13 (IO_L12P_T1_MRCC_15)
unnamed: RN28.4 (1), U1.C13 (IO_L12N_T1_MRCC_15)
unnamed: RN29.1, U1.E13 (IO_L13N_T2_MRCC_15)
unnamed: RN34.2 (1), U1.J15 (IO_L23P_T3_FOE_B_15)
unnamed: RN29.3 (1), U1.E11 (IO_L14P_T2_SRCC_15)
unnamed: RN29.4 (1), U1.D11 (IO_L14N_T2_SRCC_15)
unnamed: RN30.2 (1), U1.D14 (IO_L15P_T2_DQS_15)
unnamed: RN30.1, U1.D15 (IO_L15N_T2_DQS_ADV_B_15)
unnamed: RN30.3 (1), U1.F12 (IO_L16P_T2_A28_15)
unnamed: RN30.4 (1), U1.F13 (IO_L16N_T2_A27_15)
unnamed: RN31.1, U1.E16 (IO_L17P_T2_A26_15)
unnamed: RN31.3 (1), U1.D16 (IO_L17N_T2_A25_15)
unnamed: RN31.2 (1), U1.F15 (IO_L18P_T2_A24_15)
unnamed: RN31.4 (1), U1.E15 (IO_L18N_T2_A23_15)
unnamed: RN34.1, U1.J16 (IO_L23N_T3_FWE_B_15)
unnamed: RN33.3 (1), U1.G16 (IO_L22N_T3_A16_15)
unnamed: RN33.4 (1), U1.H16 (IO_L22P_T3_A17_15)
unnamed: IC6.38 (P1_6), RN21.1
unnamed: RN33.1, U1.G14 (IO_L21P_T3_DQS_15)
unnamed: RN33.2 (1), U1.F14 (IO_L21N_T3_DQS_A18_15)
unnamed: RN34.3 (1), U1.H14 (IO_L24P_T3_RS1_15)
unnamed: RN34.4 (1), U1.G15 (IO_L24N_T3_RS0_15)
unnamed: IC16.34 (A9), RN39.3 (1)
unnamed: IC16.33 (A8), RN39.2 (1)
unnamed: IC16.36 (A12), R21.2
unnamed: IC16.19 (\CS), R65.1, RN44.4 (1)
unnamed: IC16.37 (CKE), R55.2
unnamed: IC16.53 (DQ15), RN43.1
unnamed: IC16.51 (DQ14), RN43.2 (1)
unnamed: IC16.50 (DQ13), RN43.3 (1)
unnamed: IC16.48 (DQ12), RN43.4 (1)
unnamed: IC16.47 (DQ11), RN42.1
unnamed: IC16.45 (DQ10), RN42.2 (1)
unnamed: IC16.44 (DQ9), RN42.3 (1)
unnamed: IC16.42 (DQ8), RN42.4 (1)
unnamed: IC16.13 (DQ7), RN41.1
unnamed: IC16.11 (DQ6), RN41.2 (1)
unnamed: IC16.10 (DQ5), RN41.3 (1)
unnamed: IC16.8 (DQ4), RN41.4 (1)
unnamed: IC16.5 (DQ2), RN40.2 (1)
unnamed: IC16.4 (DQ1), RN40.3 (1)
unnamed: RN44.6 (2), U1.P6 (IO_25_14)
unnamed: RN44.5 (2), U1.T7 (IO_L21P_T3_DQS_14)
unnamed: RN44.8 (2), U1.R13 (IO_L16P_T2_CSI_B_14)
unnamed: D42.3 (1), L4.1, X8.2
PROGRAM_B: R9.2, R17.1, S1.3, S1.4 (P1), U1.L9 (PROGRAM_B_0)
PROGRAM_B1: C88.2, D3.A, R37.2, S2.1 (S), U$1.3 (NRST)
PROGRAM_B2: C91.2, D37.A, IC6.20 (RESET_N), R38.2, S3.1 (S)
RAM_ADDRESS0: RN37.8 (2), U1.P4 (IO_L5P_T0_34)
RAM_ADDRESS1: RN37.7 (2), U1.N1 (IO_L4P_T0_34)
RAM_ADDRESS2: RN37.6 (2), U1.P3 (IO_L5N_T0_34)
RAM_ADDRESS3: RN37.5 (2), U1.T4 (IO_L9P_T1_DQS_34)
RAM_ADDRESS4: RN38.5 (2), U1.T2 (IO_L8N_T1_34)
RAM_ADDRESS5: RN38.6 (2), U1.R1 (IO_L7N_T1_34)
RAM_ADDRESS6: RN38.7 (2), U1.R2 (IO_L7P_T1_34)
RAM_ADDRESS7: RN38.8 (2), U1.N4 (IO_L6N_T0_VREF_34)
RAM_ADDRESS8: RN39.7 (2), U1.T3 (IO_L9N_T1_DQS_34)
RAM_ADDRESS9: RN39.6 (2), U1.P1 (IO_L4N_T0_34)
RAM_ADDRESS10: RN39.8 (2), U1.R3 (IO_L8P_T1_34)
RAM_ADDRESS11: RN39.5 (2), U1.P5 (IO_L10P_T1_34)
RAM_ADDRESS12: R21.1, U1.M5 (IO_L6P_T0_34)
RAM_CCLK: R20.1, U1.P10 (IO_L14P_T2_SRCC_14)
RAM_CKE: R55.1, U1.P11 (IO_L14N_T2_SRCC_14)
RAM_CS: RN44.7 (2), U1.K12 (IO_0_14)
RAM_DATA0: RN40.8 (2), U1.T13 (IO_L16N_T2_A15_D31_14)
RAM_DATA1: RN40.7 (2), U1.R11 (IO_L17N_T2_A13_D29_14)
RAM_DATA2: RN40.6 (2), U1.R10 (IO_L17P_T2_A14_D30_14)
RAM_DATA3: RN40.5 (2), U1.N9 (IO_L18P_T2_A12_D28_14)
RAM_DATA4: RN41.5 (2), U1.T10 (IO_L22N_T3_A04_D20_14)
RAM_DATA5: RN41.6 (2), U1.P9 (IO_L18N_T2_A11_D27_14)
RAM_DATA6: RN41.7 (2), U1.T9 (IO_L22P_T3_A05_D21_14)
RAM_DATA7: RN41.8 (2), U1.R8 (IO_L20N_T3_A07_D23_14)
RAM_DATA8: RN42.5 (2), U1.T8 (IO_L21N_T3_DQS_A06_D22_14)
RAM_DATA9: RN42.6 (2), U1.P8 (IO_L20P_T3_A08_D24_14)
RAM_DATA10: RN42.7 (2), U1.R7 (IO_L24N_T3_A00_D16_14)
RAM_DATA11: RN42.8 (2), U1.R6 (IO_L24P_T3_A01_D17_14)
RAM_DATA12: RN43.5 (2), U1.T5 (IO_L23N_T3_A02_D18_14)
RAM_DATA13: RN43.6 (2), U1.R5 (IO_L23P_T3_A03_D19_14)
RAM_DATA14: RN43.7 (2), U1.N6 (IO_L19N_T3_A09_D25_VREF_14)
RAM_DATA15: RN43.8 (2), U1.M6 (IO_L19P_T3_A10_D26_14)
SLOT_I2C_SCL1: D8.4 (2), RN17.3 (1), X1.A1, X2.B1, X3.A1, X4.B1
SLOT_I2C_SDA1: D8.3 (1), RN17.4 (1), X1.A2, X2.B2, X3.A2, X4.B2
SLOT_SPI_CLK: D7.6 (4), RN16.7 (2), X1.B1, X2.A1, X4.A1
SLOT_SPI_CS3: D5.4 (3), RN2.8 (2), X1.A3, X2.A4
SLOT_SPI_CS4: D5.6 (4), RN2.7 (2), X1.A4, X4.A4
SLOT_SPI_MISO: D7.3 (2), RN16.5 (2), X1.B3, X2.A3, X4.A3
SLOT_SPI_MOSI: D7.1, RN16.6 (2), X1.B2, X2.A2, X4.A2
SPI_CLK: IC10.SCL, RN16.2 (1), U1.N11 (IO_L13P_T2_MRCC_14), U$1.7 (SPI_CLK)
SPI_CS1(LT2947): IC10.AD1/CS, U$1.23 (SPI_CS1)
SPI_MISO: IC10.SDO, RN16.4 (1), U1.M15 (IO_L3N_T0_DQS_EMCCLK_14), U$1.10 (SPI_MISO)
SPI_MOSI: IC10.SDI, RN16.3 (1), U1.R15 (IO_L9P_T1_DQS_14), U$1.8 (SPI_MOSI)
USB_PORT3_DM: U$8.4 (D2(C)), X2.B4, X3.A4, X4.B4, X7.2
USB_PORT3_DP: U$8.6 (D1(C)), X2.B3, X3.A3, X4.B3, X7.3
USB_PORT4_DM: U$7.4 (D2(C)), X6.2
USB_PORT4_DP: U$7.6 (D1(C)), X6.3
VIN: C67.1, C68.1, C160.1, C161.1, IC7.PVIN1, IC7.PVIN2, IC7.VIN, IC8.PVIN1, IC8.PVIN2, IC8.VIN, IC10.IM_1 (IM), IC10.IM_2 (IM), IC10.IM_3 (IM), IC10.IM_4 (IM), IC10.IM_5 (IM), IC10.IM_6 (IM), R85.2, R97.2, R120.2
XADC_GND: C45.2, L2.1, U1.G7 (GNDADC_0), U1.H7 (VREFN_0), U1.H8 (VP_0), U1.J7 (VN_0), U1.J8 (VREFP_0)

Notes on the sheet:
VCORE Ausgang liefert 1V8 keine Verb. notwendig
Port A: High-Speed (USB-Hub) Port B: High-Speed (WLAN-Modul) Port C: Full-Speed (Display) Hinweis: (microUSB Buchse kann nicht mehr verwendet werden)
Eingangsspannung
12V
Umschalter Intern/Extern
U,I,P Messung mit SPI Schnittstelle
Step Down Converter
Lademmodul
Injection Point 8x
FPGA I/O für SLOTs werden über VCC_EXT betrieben
X3(SLOT3) ANALOG/DIGITAL Peripherie X4(SLOT4) Taster/LEDs/...
BLUETOOTH I/O Ports (12 Bit) Verbindungen auf externe Slots
RESERVE
X2(SLOT2) Reserve X4(SLOT4) I/O Expansion
X1(SLOT1) SOUND/VGA X3(SLOT3) ANALOG
SPI BUS an Slots nur verfügbar wenn SOUNDKARTE und I2C nicht aktiviert!
Wenn SPI Bus/I2S inaktiv I2C Bus 0 auf CS3/4 verfügbar!
NUF2221W1 ESD-Schutz für externe USB Buchsen
Verbindung zu Antenne in 50 Ohm Technik ausführen (50 Ohm Leiterbahn)
Antennenbauteile müssen so nahe wie möglich an den Eingängen positioniert werden! (möglicherweise mit Abschirmung)
SMBUSZ=1 (I²C EEPROM) SMBUSZ=0 (SMBUS Host)
Testpunkt
max. Schreibgeschwindigkeit 33MHz!
max. Taktfrequenz 167MHz
FIFO max. Übertragungs- geschwindigkeit 1MBit/s
CCLK1=100MHz CCLK2=24.576MHz
Linux Serial Console
*Widerstandspositionierung (FPGA<->SDRAM) mittig für Datenbus (DQ,DQS), CLK, CKE; *Widerstandspositionierung (FPGA<->SDRAM) nahe am FPGA für unidirektionale Leitungen, Adressbus, Steuerbus
Widerstand konfiguriert Device als USB Fullspeed
Widerstand konfiguriert Device als USB Fullspeed . Bei diesem Chip nicht notwendig da bereits integriert daher nicht bestückt!
Nicht bestückt
Leitungsimpedanz für Standard I/O 100Ohm (25+75) Leitungsimpedanz für Leistungs I/O 75 Ohm (25+50)
L=350n Type = BLM18PG221SN1D

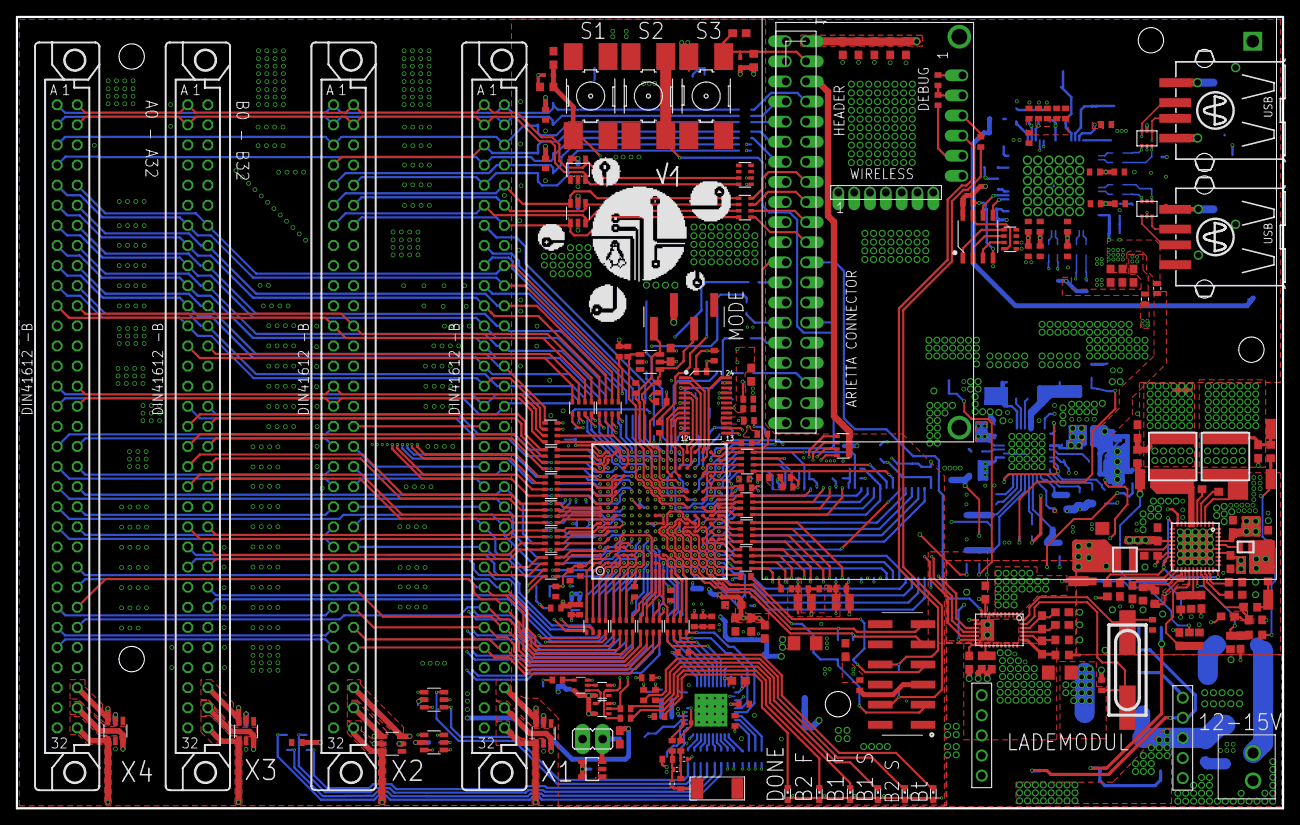
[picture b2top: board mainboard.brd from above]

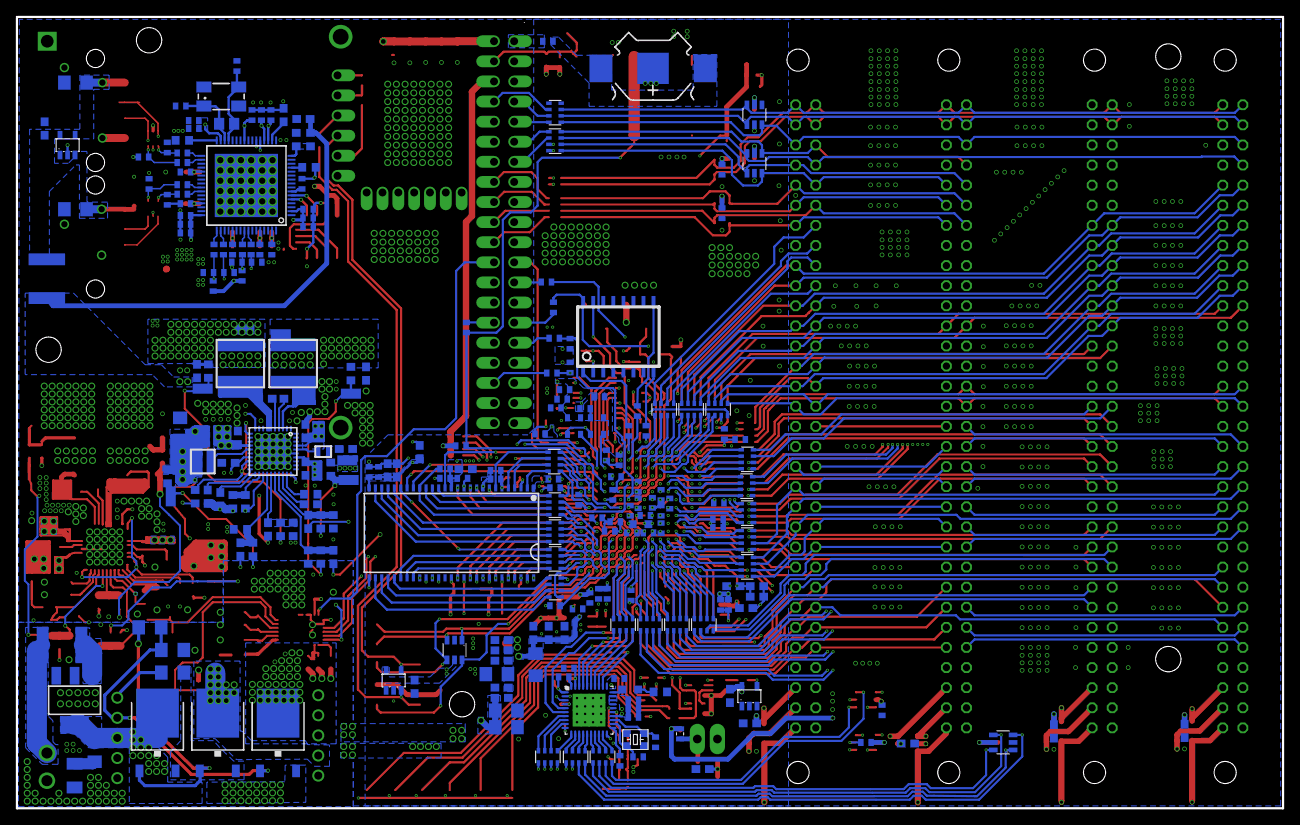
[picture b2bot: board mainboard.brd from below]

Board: 6 copper layers, 160.0 x 100.0 mm, 485 parts (245 on the bottom side), 515 nets.
